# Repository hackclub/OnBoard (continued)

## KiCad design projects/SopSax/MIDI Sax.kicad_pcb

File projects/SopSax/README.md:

---
name: "Stefan Lighezan"
slack_handle: "@Stefan Lighezan"
github_handle: "@stefanlighezan"
tutorial: "https://github.com/Whackalenso/CircuitSax"
---

# SopSax

<!-- Describe your board in 2-3 sentences. What are you making? What will it do? -->
It is a digital soprano sax pcb. It requires external soldering and 3D printed keys to work, but this is the mechanical aspect. It will be able to work with DAWs, and Musescore. Another feature that I added to this was a UI Menu that controls some of the features such as various aspects of tone production and intonation.
<!-- How much is it going to cost? -->
About $30, but shipping drives the price up like crazy
<!-- Tell us a little bit about your design process. What were some challenges? What helped? ***Totally optional*** -->
I followed Whackalenso's tutorial for creating a soprano saxophone and gave him attribution, all with his consent. One challenge was making this something that I could use to practice as an alternative to my alto saxophone. I made a UI and used "SoundFonts", which were scripts that controlled various aspects of tone, and I was able to parse it, allowing me to have a soprano sax sound that is decent (which obviously you cannot do on alto saxophone). This is a project I am very invested in because my parents do not want me to practice at home because it creates too much noise. This instrument allows me to practice at my own will and keep my parents happy.

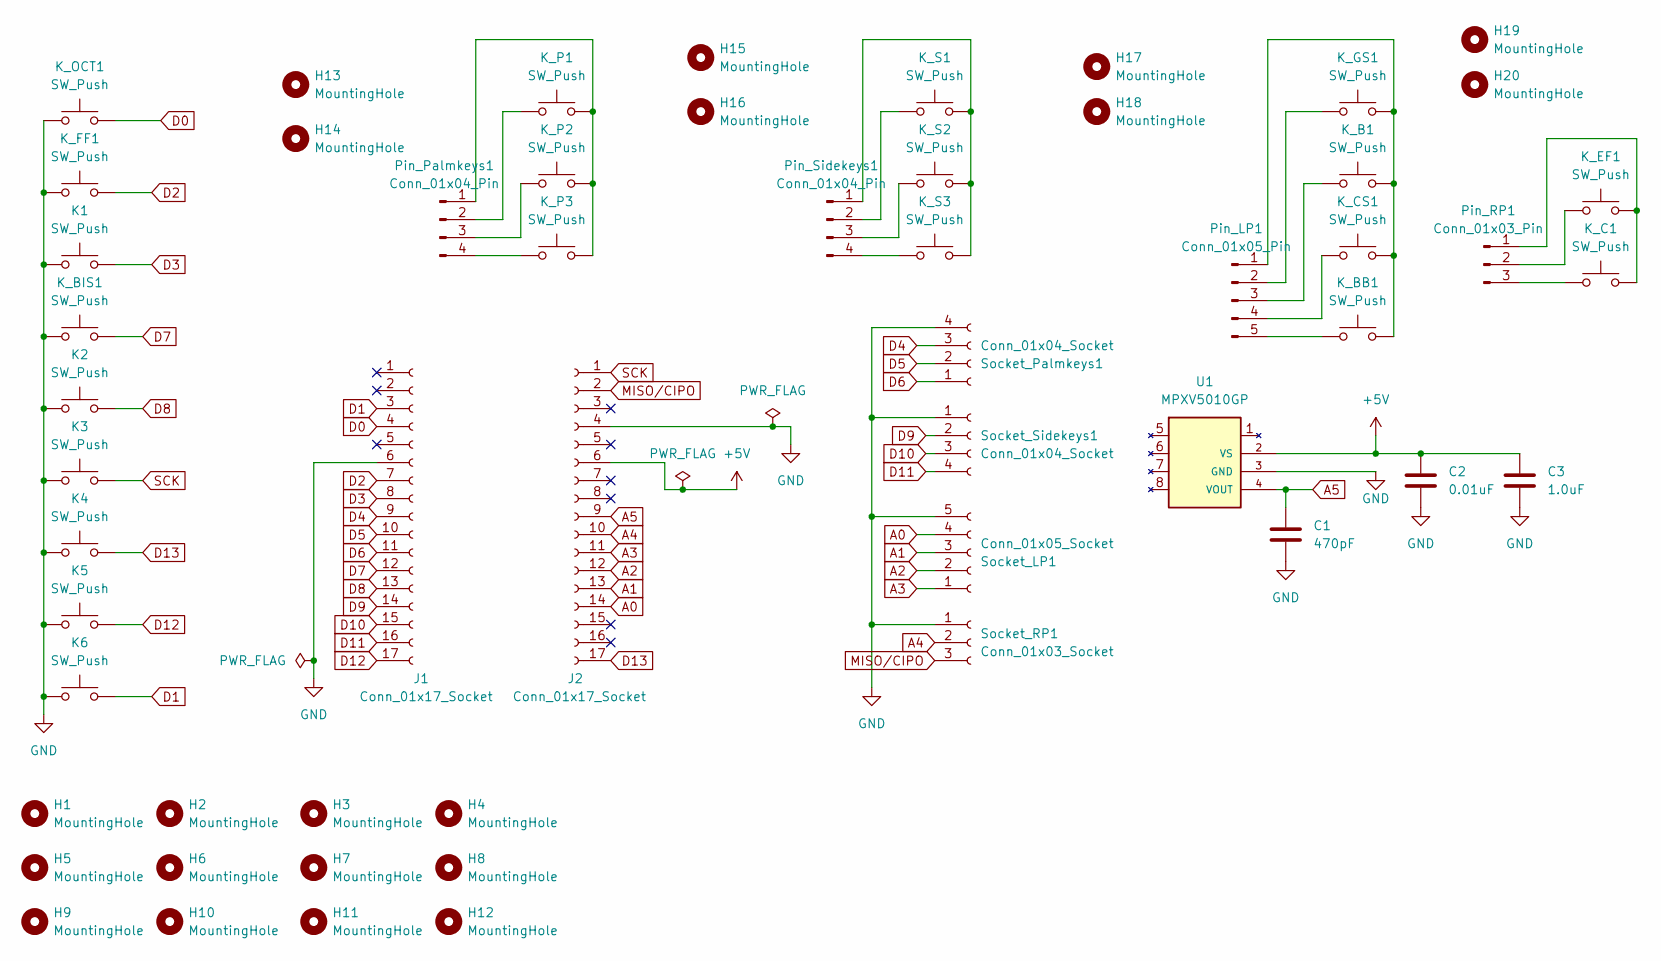
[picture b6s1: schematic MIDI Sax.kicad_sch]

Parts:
C1: 470pF; C_1206_3216Metric
C2: 0.01uF; C_1206_3216Metric
C3: 1.0uF; C_1206_3216Metric
H1, H2, H3, H4, H5, H6, H9, H10, H11, H12, H13, H14, H17, H18: MountingHole; MountingHole_2.85mm
H7, H8, H15, H16, H19, H20: MountingHole; MountingHole_3.3mm
J1, J2: Conn_01x17_Socket; PinSocket_1x17_P2.54mm_Vertical
K1, K2, K3, K4, K5, K6: SW_Push; SW_Cherry_MX_PCB
K_B1: SW_Push; SW_Cherry_MX_PCB
K_BB1: SW_Push; SW_Cherry_MX_PCB
K_BIS1: SW_Push; SW_Cherry_MX_PCB
K_C1: SW_Push; SW_Cherry_MX_PCB
K_CS1: SW_Push; SW_Cherry_MX_PCB
K_EF1: SW_Push; SW_Cherry_MX_PCB
K_FF1: SW_Push; SW_Cherry_MX_PCB
K_GS1: SW_Push; SW_Cherry_MX_PCB
K_OCT1: SW_Push; SW_Cherry_MX_PCB
K_P1, K_P2, K_P3: SW_Push; SW_Cherry_MX_PCB
K_S1, K_S2, K_S3: SW_Push; SW_Cherry_MX_PCB
Pin_LP1: Conn_01x05_Pin; SAMTEC_TSM-105-01-L-SH
Pin_Palmkeys1: Conn_01x04_Pin; PinHeader_1x04_P2.54mm_Vertical
Pin_RP1: Conn_01x03_Pin; CONN3_M20-8900_HRW
Pin_Sidekeys1: Conn_01x04_Pin; PinHeader_1x04_P2.54mm_Vertical
Socket_LP1: Conn_01x05_Socket; HARWIN_M20-7910542R
Socket_Palmkeys1: Conn_01x04_Socket; HARWIN_M20-7910442R
Socket_RP1: Conn_01x03_Socket; HARWIN_M20-7910342R
Socket_Sidekeys1: Conn_01x04_Socket; HARWIN_M20-7910442R
U1: MPXV5010GP; SOIC254P1821X762-8N

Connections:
+5V: C2.1, C3.1, J2.6, U1.2 (VS)
A0: J2.14, Socket_LP1.4
A1: J2.13, Socket_LP1.3
A2: J2.12, Socket_LP1.2
A3: J2.11, Socket_LP1.1
A4: J2.10, Socket_RP1.2
A5: C1.1, J2.9, U1.4 (VOUT)
D0: J1.4, K_OCT1.2
D1: J1.3, K6.2
D2: J1.7, K_FF1.2
D3: J1.8, K1.2
D4: J1.9, Socket_Palmkeys1.3
D5: J1.10, Socket_Palmkeys1.2
D6: J1.11, Socket_Palmkeys1.1
D7: J1.12, K_BIS1.2
D8: J1.13, K2.2
D9: J1.14, Socket_Sidekeys1.2
D10: J1.15, Socket_Sidekeys1.3
D11: J1.16, Socket_Sidekeys1.4
D12: J1.17, K5.2
D13: J2.17, K4.2
GND: C1.2, C2.2, C3.2, J1.6, J2.4, K1.1, K2.1, K3.1, K4.1, K5.1, K6.1, K_BIS1.1, K_FF1.1, K_OCT1.1, Socket_LP1.5, Socket_Palmkeys1.4, Socket_RP1.1, Socket_Sidekeys1.1, U1.3 (GND)
MISO/CIPO: J2.2, Socket_RP1.3
unnamed: K_B1.2, K_BB1.2, K_CS1.2, K_GS1.2, Pin_LP1.1
unnamed: K_GS1.1, Pin_LP1.2
unnamed: K_B1.1, Pin_LP1.3
unnamed: K_CS1.1, Pin_LP1.4
unnamed: K_BB1.1, Pin_LP1.5
unnamed: K_P1.2, K_P2.2, K_P3.2, Pin_Palmkeys1.1
unnamed: K_P1.1, Pin_Palmkeys1.2
unnamed: K_P2.1, Pin_Palmkeys1.3
unnamed: K_P3.1, Pin_Palmkeys1.4
unnamed: K_C1.2, K_EF1.2, Pin_RP1.1
unnamed: K_EF1.1, Pin_RP1.2
unnamed: K_C1.1, Pin_RP1.3
unnamed: K_S1.2, K_S2.2, K_S3.2, Pin_Sidekeys1.1
unnamed: K_S1.1, Pin_Sidekeys1.2
unnamed: K_S2.1, Pin_Sidekeys1.3
unnamed: K_S3.1, Pin_Sidekeys1.4
SCK: J2.1, K3.2

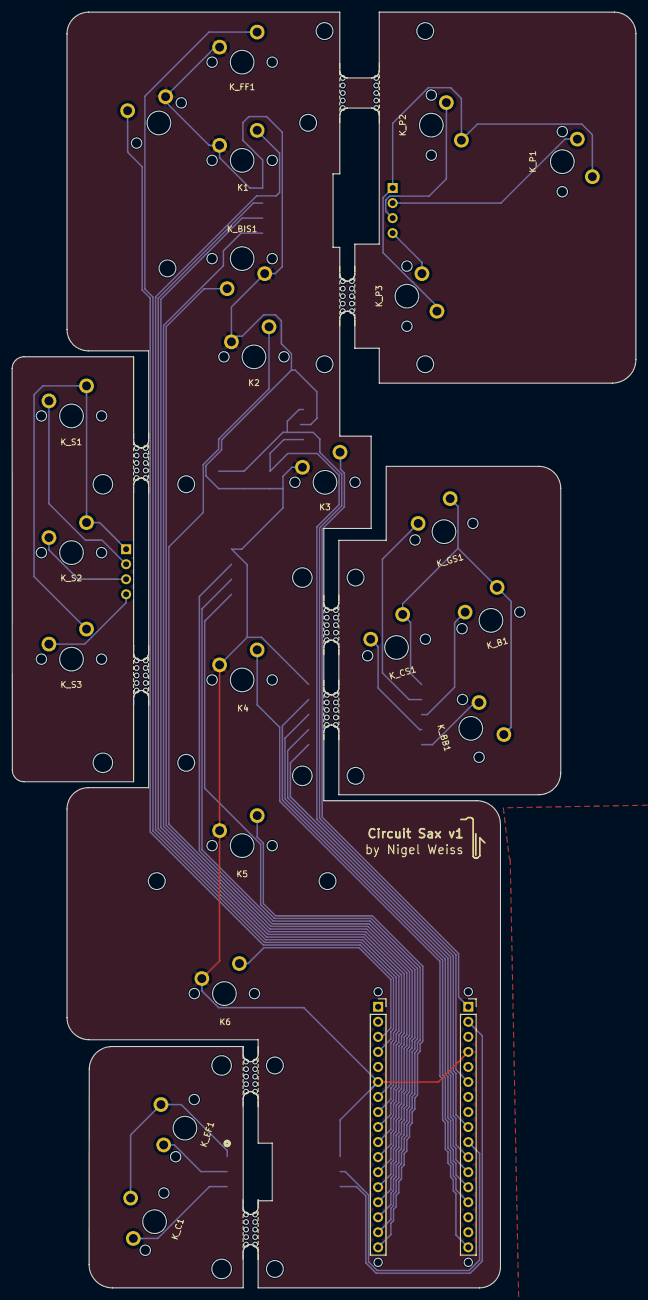
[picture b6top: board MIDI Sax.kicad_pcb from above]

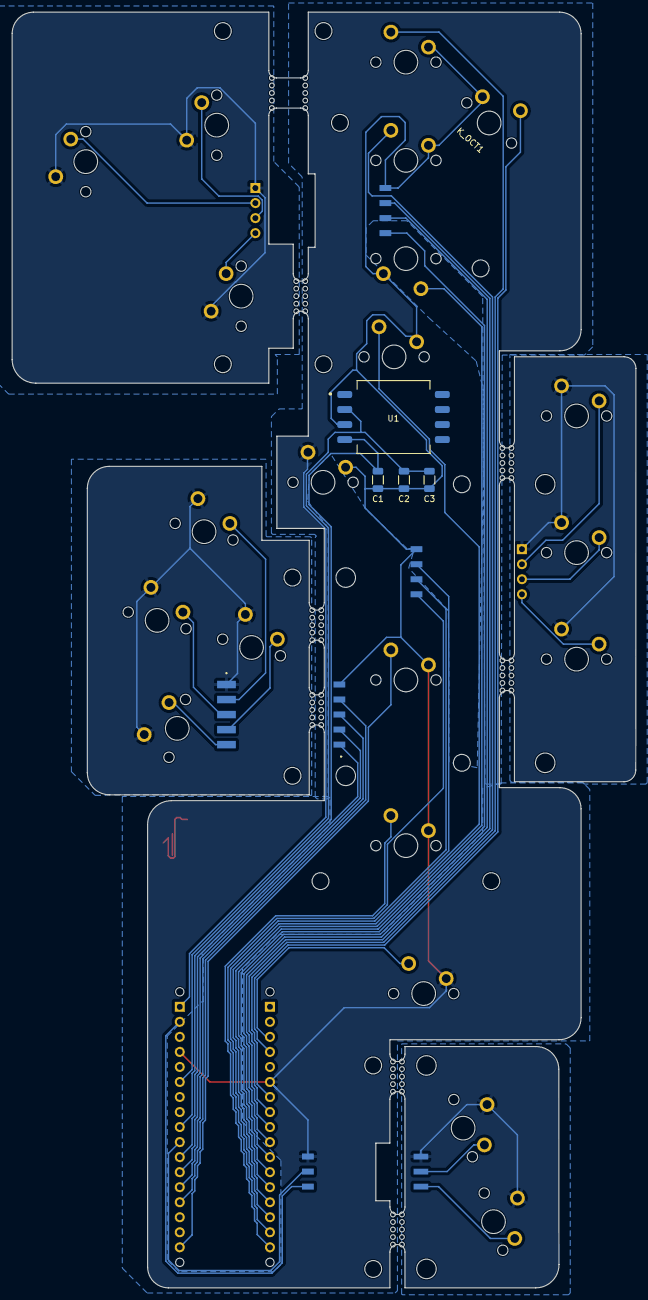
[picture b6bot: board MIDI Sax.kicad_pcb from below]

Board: 2 copper layers, 105.4 x 215.6 mm, 75 parts (13 on the bottom side), 40 nets.

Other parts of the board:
H1#2, H1#3, H1#4, H1#5: MountingHole; MountingHole_1.4mm
TAB4, TAB4#2, TAB4#3, TAB4#4, TAB4#5, TAB4#6, TAB4#7, TAB4#8, TAB4#9, TAB4#10, TAB4#11, TAB4#12, TAB4#13, TAB4#14, TAB4#15, TAB4#16: Mouse Bites; Breakout tab

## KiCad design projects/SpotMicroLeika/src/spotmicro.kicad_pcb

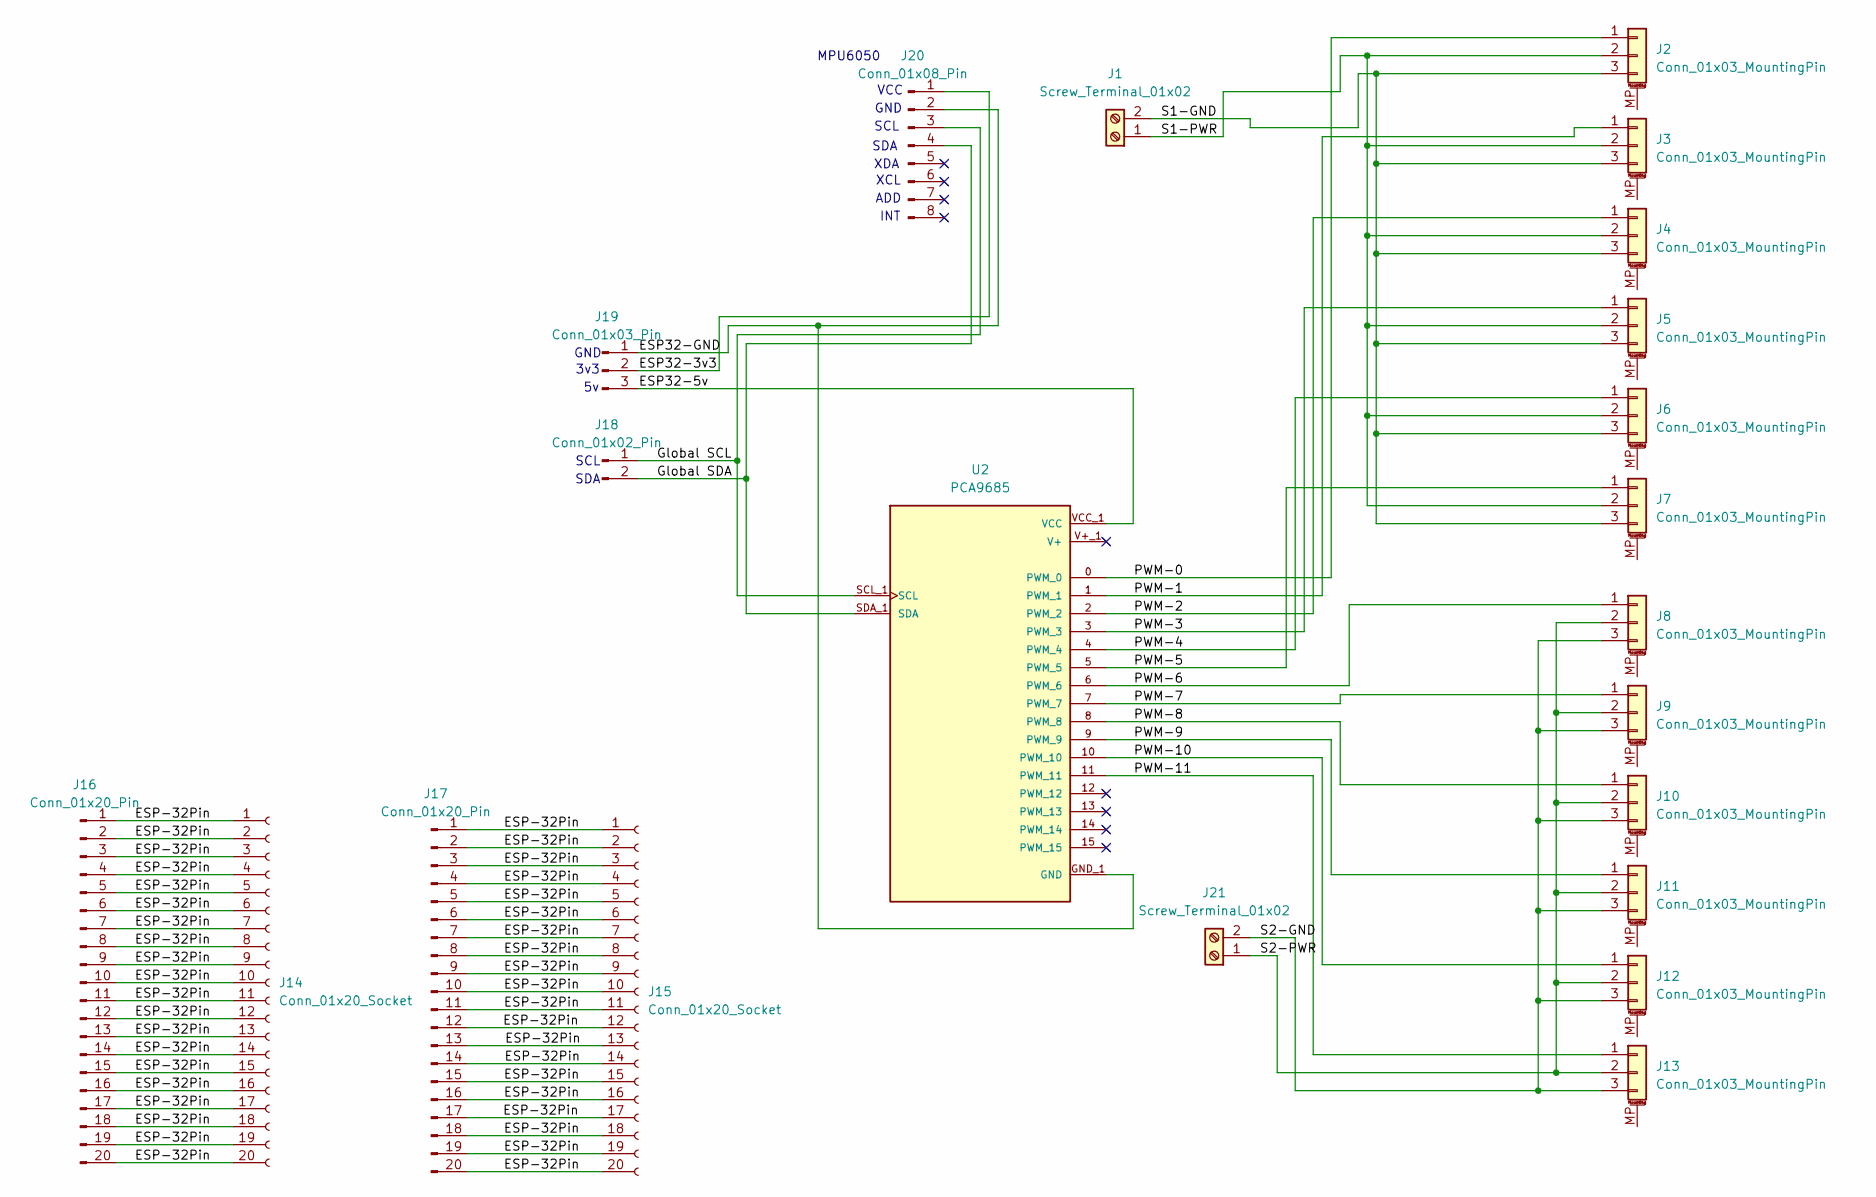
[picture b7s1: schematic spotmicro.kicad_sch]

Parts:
J1, J21: Screw_Terminal_01x02; TerminalBlock_Phoenix_MKDS-1,5-2_1x02_P5.00mm_Horizontal
J2, J3, J4, J5, J6, J7, J8, J9, J10, J11, J12, J13: Conn_01x03_MountingPin; PinHeader_1x03_P2.54mm_Vertical
J14, J15: Conn_01x20_Socket; PinSocket_1x20_P2.54mm_Vertical
J16, J17: Conn_01x20_Pin; PinHeader_1x20_P2.54mm_Vertical
J18: Conn_01x02_Pin; PinSocket_1x02_P2.54mm_Vertical
J19: Conn_01x03_Pin; PinSocket_1x03_P2.54mm_Vertical
J20: Conn_01x08_Pin; PinSocket_1x08_P2.54mm_Vertical
U2: PCA9685; MODULE_815; PARTREV C

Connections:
/ESP32-3v3: J19.2, J20.1
/ESP32-5v: J19.3, U2.VCC_1 (VCC)
/ESP32-GND: J19.1, J20.2, U2.GND_1 (GND)
/ESP-32Pin: J14.1, J14.2, J14.3, J14.4, J14.5, J14.6, J14.7, J14.8, J14.9, J14.10, J14.11, J14.12, J14.13, J14.14, J14.15, J14.16, J14.17, J14.18, J14.19, J14.20, J15.1, J15.2, J15.3, J15.4, J15.5, J15.6, J15.7, J15.8, J15.9, J15.10, J15.11, J15.12, J15.13, J15.14, J15.15, J15.16, J15.17, J15.18, J15.19, J15.20, J16.1, J16.2, J16.3, J16.4, J16.5, J16.6, J16.7, J16.8, J16.9, J16.10, J16.11, J16.12, J16.13, J16.14, J16.15, J16.16, J16.17, J16.18, J16.19, J16.20, J17.1, J17.2, J17.3, J17.4, J17.5, J17.6, J17.7, J17.8, J17.9, J17.10, J17.11, J17.12, J17.13, J17.14, J17.15, J17.16, J17.17, J17.18, J17.19, J17.20
/Global SCL: J18.1, J20.3, U2.SCL_1 (SCL)
/Global SDA: J18.2, J20.4, U2.SDA_1 (SDA)
/PWM-0: J2.1, U2.0 (PWM_0)
/PWM-1: J3.1, U2.1 (PWM_1)
/PWM-2: J4.1, U2.2 (PWM_2)
/PWM-3: J5.1, U2.3 (PWM_3)
/PWM-4: J6.1, U2.4 (PWM_4)
/PWM-5: J7.1, U2.5 (PWM_5)
/PWM-6: J8.1, U2.6 (PWM_6)
/PWM-7: J9.1, U2.7 (PWM_7)
/PWM-8: J10.1, U2.8 (PWM_8)
/PWM-9: J11.1, U2.9 (PWM_9)
/PWM-10: J12.1, U2.10 (PWM_10)
/PWM-11: J13.1, U2.11 (PWM_11)
/S1-GND: J1.2, J2.3, J3.3, J4.3, J5.3, J6.3, J7.3
/S1-PWR: J1.1, J2.2, J3.2, J4.2, J5.2, J6.2, J7.2
/S2-GND: J8.3, J9.3, J10.3, J11.3, J12.3, J13.3, J21.2
/S2-PWR: J8.2, J9.2, J10.2, J11.2, J12.2, J13.2, J21.1

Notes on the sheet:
SDA
GND
XCL
MPU6050
VCC
INT
SCL
3v3
XDA
ADD

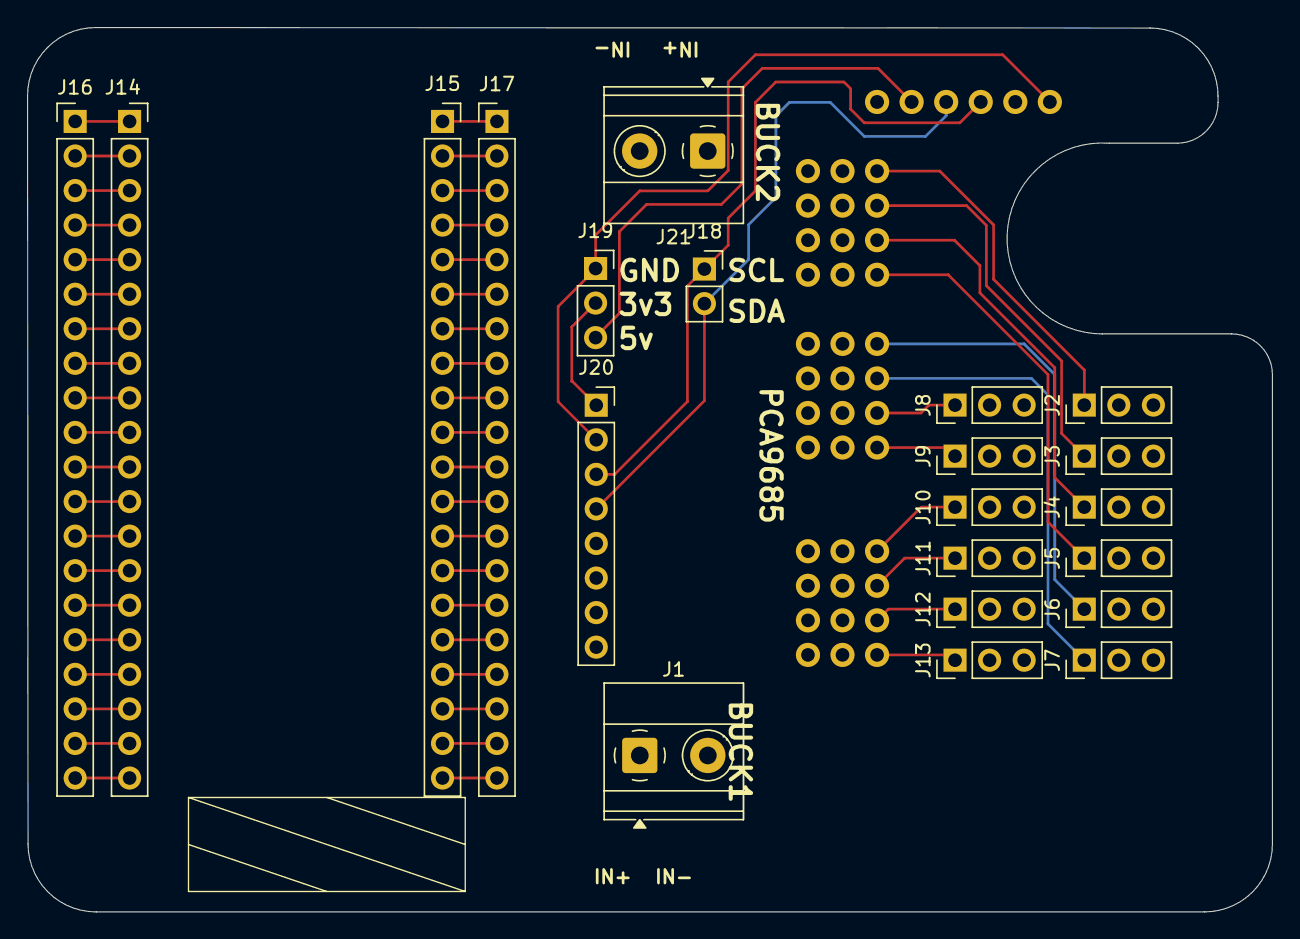
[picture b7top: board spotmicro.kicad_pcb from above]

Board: 4 copper layers, 91.5 x 65.0 mm, 22 parts (0 on the bottom side), 22 nets.
